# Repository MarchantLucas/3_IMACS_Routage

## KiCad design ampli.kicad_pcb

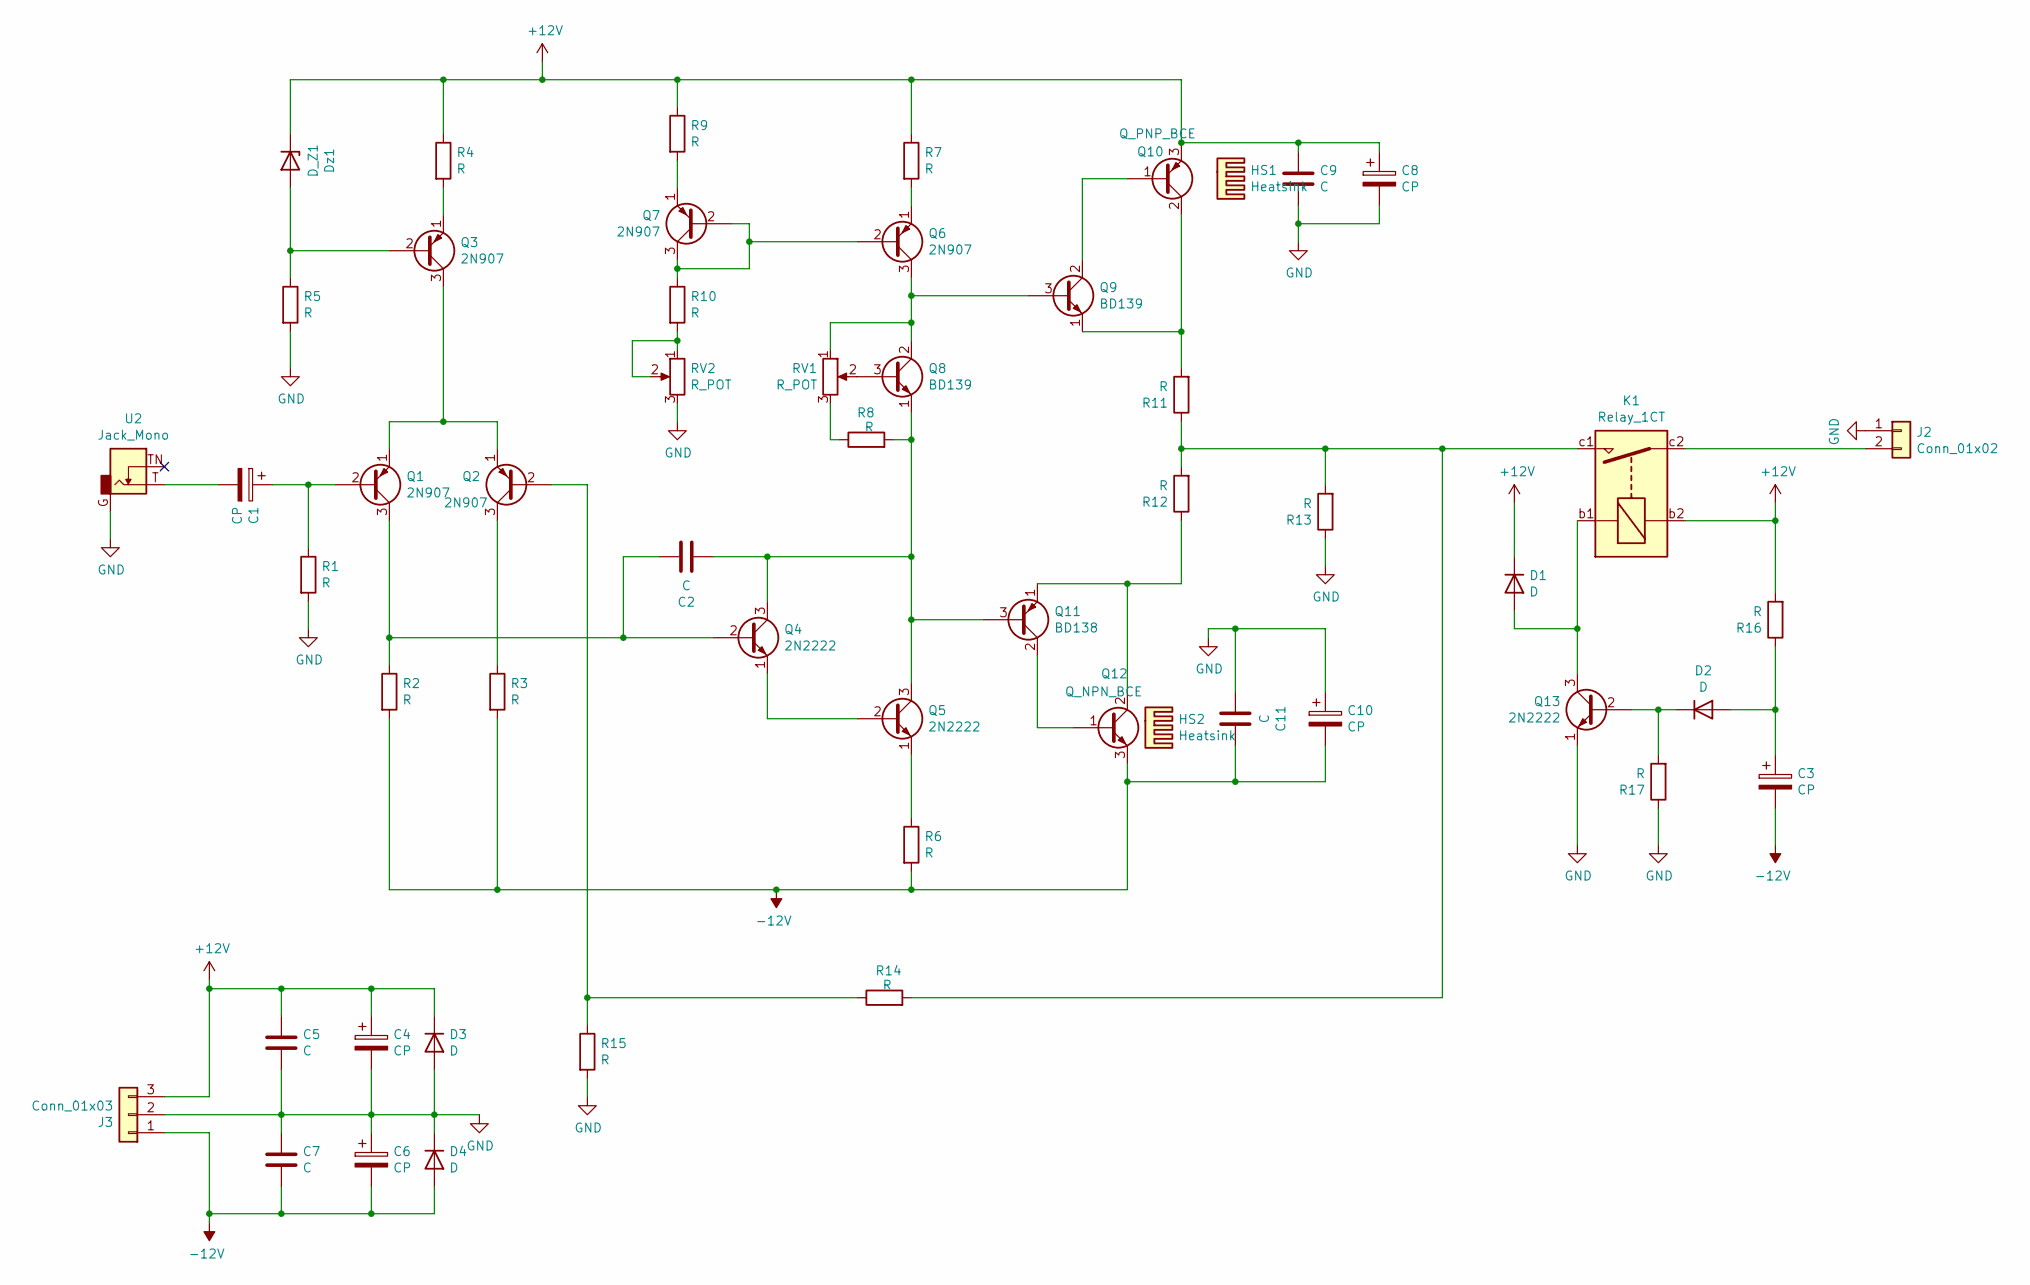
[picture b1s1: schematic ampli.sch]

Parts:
C1, C3, C4, C6: CP; CP_Radial_D8.0mm_P5.00mm
C2, C5, C7, C9, C11: C; C_Rect_L7.2mm_W3.5mm_P5.00mm_FKS2_FKP2_MKS2_MKP2
C8, C10: CP; CP_Radial_D12.5mm_P5.00mm
D1, D2, D3, D4: D; D_DO-35_SOD27_P10.16mm_Horizontal
Dz1: D_Z1; D_DO-35_SOD27_P10.16mm_Horizontal
HS1, HS2: Heatsink; Heatsink_Fischer_SK104-STC-STIC_35x13mm_2xDrill2.5mm
J2: Conn_01x02; PhoenixContact_MSTBVA_2,5_2-G-5,08_1x02_P5.08mm_Vertical
J3: Conn_01x03; PhoenixContact_MSTBVA_2,5_3-G-5,08_1x03_P5.08mm_Vertical
K1: Relay_1CT; Relay_112LMH2
Q1, Q2, Q3, Q6, Q7: 2N907; TO-18-3
Q4, Q5, Q13: 2N2222; TO-18-3
Q8, Q9: BD139; TO-126-3_Vertical
Q10: Q_PNP_BCE; TO-220-3_Vertical
Q11: BD138; TO-126-3_Vertical
Q12: Q_NPN_BCE; TO-220-3_Vertical
R1, R2, R3, R4, R5, R6, R7, R8, R9, R10, R13, R14, R15, R16, R17: R; R_Axial_DIN0207_L6.3mm_D2.5mm_P10.16mm_Horizontal
R11, R12: R; R_Axial_DIN0516_L15.5mm_D5.0mm_P20.32mm_Horizontal
RV1, RV2: R_POT; Potentiometer_Bourns_3296W_Vertical
U2: Jack_Mono; Jack_35RAPC2AV

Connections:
+12V: C4.1, C5.1, C8.1, C9.1, D1.1 (K), D3.1 (K), Dz1.1 (K), J3.3, K1.b2, Q10.3 (E), R4.1, R7.1, R9.1, R16.2
-12V: C3.2, C6.2, C7.2, C10.2, C11.1, D4.2 (A), J3.1, Q12.3 (E), R2.2, R3.2, R6.2
GND: C4.2, C5.2, C6.1, C7.1, C8.2, C9.2, C10.1, C11.2, D3.2 (A), D4.1 (K), J2.1, J3.2, Q13.1 (E), R1.2, R5.2, R13.1, R15.2, R17.1, RV2.3, U2.G
unnamed: C1.1, Q1.2 (B), R1.1
unnamed: C1.2, U2.T
unnamed: C2.1, Q1.3 (C), Q4.2 (B), R2.1
unnamed: C2.2, Q4.3 (C), Q5.3 (C), Q8.1 (E), Q11.3 (B), R8.2
unnamed: C3.1, D2.2 (A), R16.1
unnamed: D1.2 (A), K1.b1, Q13.3 (C)
unnamed: D2.1 (K), Q13.2 (B), R17.2
unnamed: Dz1.2 (A), Q3.2 (B), R5.1
unnamed: J2.2, K1.c2
unnamed: K1.c1, R11.1, R12.2, R13.2, R14.2
unnamed: Q1.1 (E), Q2.1 (E), Q3.3 (C)
unnamed: Q2.2 (B), R14.1, R15.1
unnamed: Q2.3 (C), R3.1
unnamed: Q3.1 (E), R4.2
unnamed: Q4.1 (E), Q5.2 (B)
unnamed: Q5.1 (E), R6.1
unnamed: Q6.1 (E), R7.2
unnamed: Q6.2 (B), Q7.2 (B), Q7.3 (C), R10.1
unnamed: Q6.3 (C), Q8.2 (C), Q9.3 (B), RV1.1
unnamed: Q7.1 (E), R9.2
unnamed: Q8.3 (B), RV1.2
unnamed: Q9.2 (C), Q10.1 (B)
unnamed: Q9.1 (E), Q10.2 (C), R11.2
unnamed: Q11.1 (E), Q12.2 (C), R12.1
unnamed: Q11.2 (C), Q12.1 (B)
unnamed: R8.1, RV1.3
unnamed: R10.2, RV2.1, RV2.2

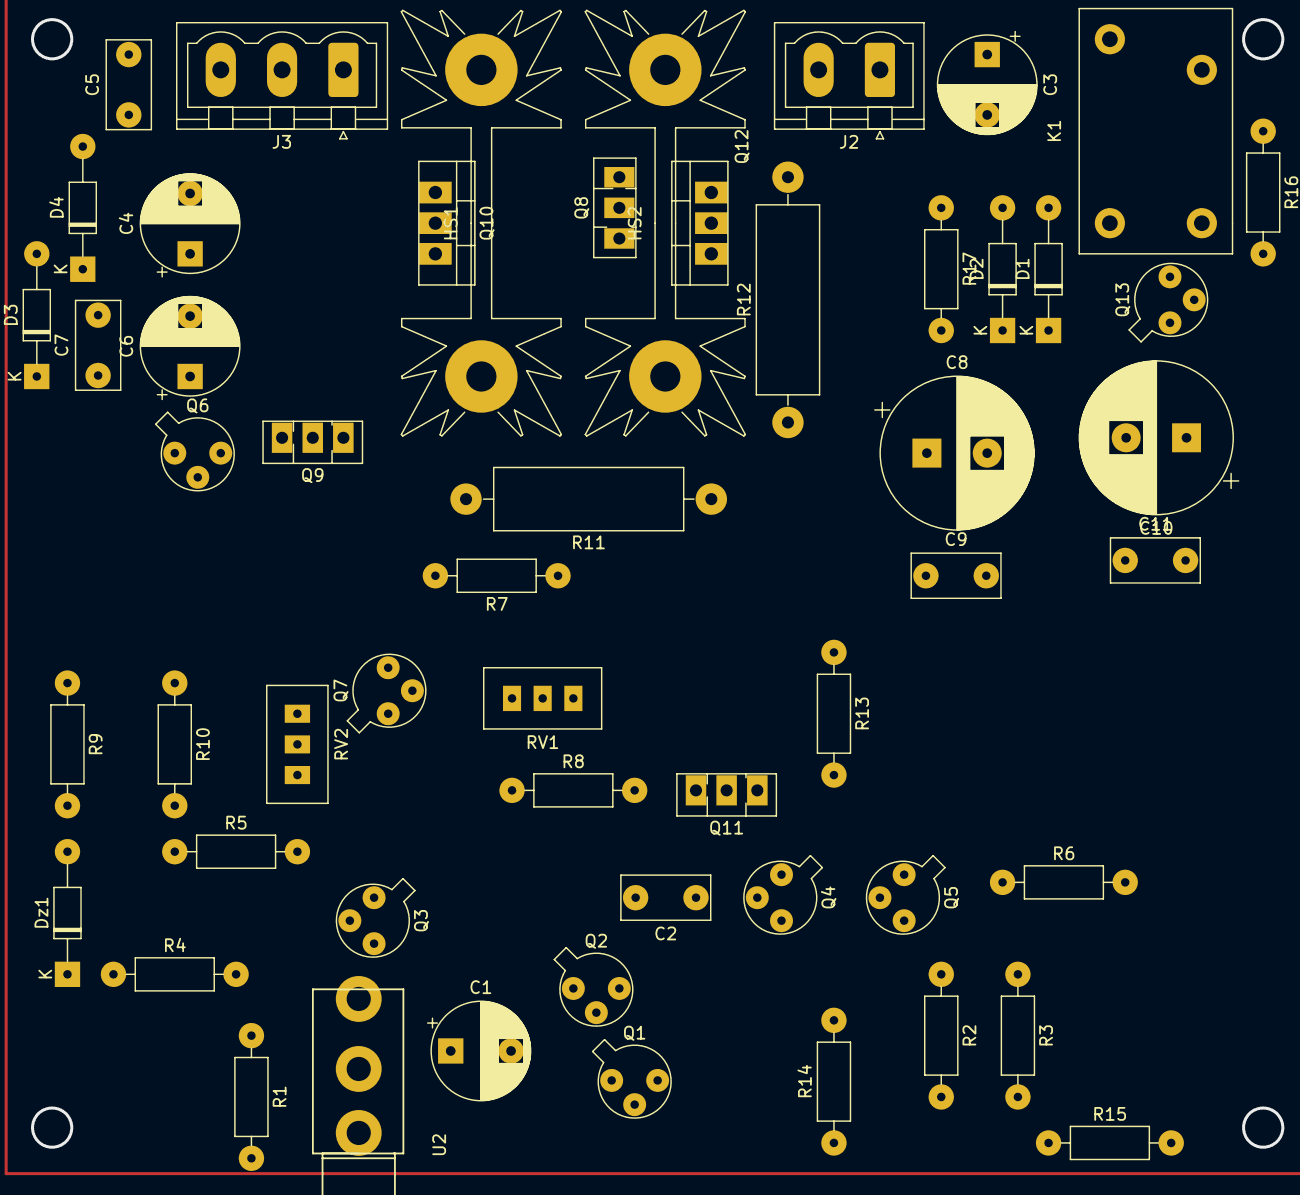
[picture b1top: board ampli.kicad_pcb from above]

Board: 2 copper layers, 54 parts (0 on the bottom side), 30 nets.

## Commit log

2021-04-06 librairie pour trouver relais
2021-04-06 Projet Kicad
2021-04-06 Utilitaire au projet
2021-04-06 PCB BACK
2021-04-06 NETLIST
2021-04-06 schema
2021-04-06 relay empreinte
2021-04-06 fichier librairie
2021-04-06 fichier librairie empreinte
2021-04-06 1er placement des composants
2021-04-13 bib_relay
2021-04-13 pcb front
2021-04-13 pcb_back
2021-04-13 cache
